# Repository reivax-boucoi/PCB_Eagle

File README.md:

# PCB
This repo contains Eagle files from personnal projects involving PCBs.

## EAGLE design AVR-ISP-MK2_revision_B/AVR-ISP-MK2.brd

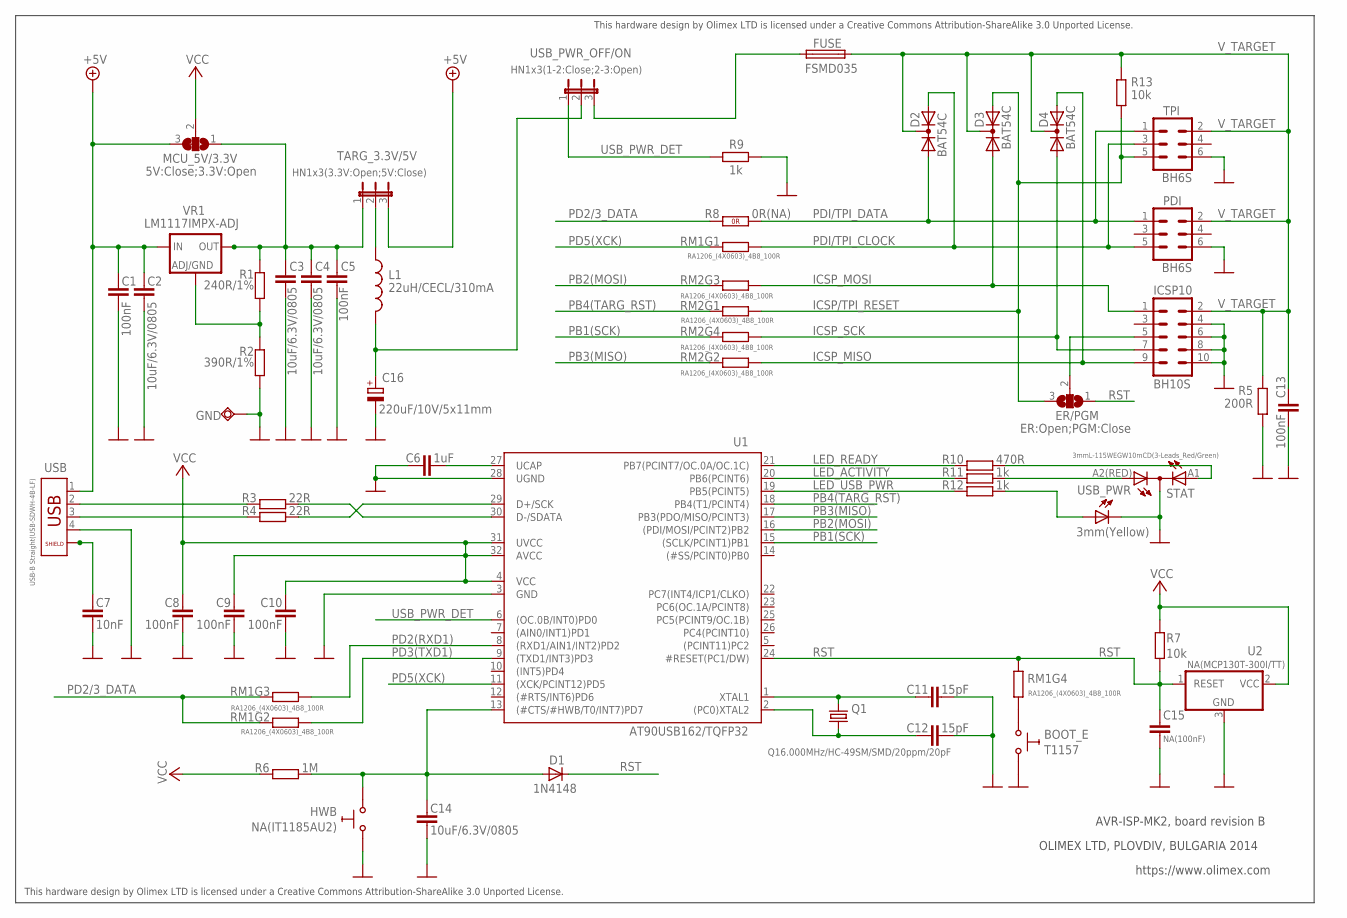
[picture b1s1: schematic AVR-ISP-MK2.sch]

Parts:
BOOT_E: T1157
C1, C5, C8, C9, C10, C13: 100nF; C0603_DWS
C2, C3, C4, C14: 10uF/6.3V/0805; C0805_5MIL_DWS
C6: 1uF; C0603_DWS
C7: 10nF; C0603_DWS
C11, C12: 15pF; C0603_DWS
C15: NA(100nF); C0603_DWS_NA
C16: 220uF/10V/5x11mm; C-SMD5X11
D1: 1N4148; MINI-MELF
D2, D3, D4: BAT54C; SOT23C
ER/PGM: ER:Open;PGM:Close; SJ_2
FUSE: FSMD035; 1206
GND: TESTPAD3; TEST_PAD40/70/SQUARE
HWB: NA(IT1185AU2); IT1185AU2
ICSP10: BH10S; ML10_PADS
L1: 22uH/CECL/310mA; L_CECL
MCU_5V/3.3V: 5V:Close;3.3V:Open; SJ_2
PDI: BH6S; ML6_PADS
Q1: Q16.000MHz/HC-49SM/SMD/20ppm/20pF; HC49/SMD2_THIN
R1: 240R/1%; R0603_5MIL_DWS
R2: 390R/1%; R0603_5MIL_DWS
R3, R4: 22R; R0603_5MIL_DWS
R5: 200R; R0805_5MIL_DWS
R6: 1M; R0603_5MIL_DWS
R7, R13: 10k; R0603_5MIL_DWS
R8: 0R(NA); 0603_0R
R9, R11, R12: 1k; R0603_5MIL_DWS
R10: 470R; R0603_5MIL_DWS
RM1, RM2: RA1206_(4X0603)_4B8_100R; R_MATRIX_4
STAT: 3mmL-115WEGW10mCD(3-Leads_Red/Green); 2X3MMLED
TARG_3.3V/5V: HN1x3(3.3V:Open;5V:Close); HN1X3-SMD_MIRROR
TPI: BH6S; ML6_PADS
U1: AT90USB162/TQFP32; TQFP32
U2: NA(MCP130T-300I/TT); SOT23
USB: USB-B Straight(USB-SDWH-4B-LF); USB_PADS
USB_PWR: 3mm(Yellow); LED-3.0MM
USB_PWR_OFF/ON: HN1x3(1-2:Close;2-3:Open); HN1X3-SMD
VR1: LM1117IMPX-ADJ; SOT223_

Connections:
+5V: C1.1, C2.1, MCU_5V/3.3V.3, TARG_3.3V/5V.3, USB.1, VR1.3 (IN)
GND: BOOT_E.2 (1), C1.2, C2.2, C3.2, C4.2, C5.2, C6.2, C7.2, C8.2, C9.2, C10.2, C11.1, C12.1, C13.2, C14.2, C15.2, C16.-, GND.P$1, HWB.2 (1), ICSP10.4, ICSP10.6, ICSP10.8, ICSP10.10, PDI.6, R2.2, R5.2, R9.1, STAT.C, TPI.6, U1.3 (GND), U1.28 (UGND), U2.3 (GND), USB.4, USB_PWR.K (C)
ICSP/TPI_RESET: D3.1 (A1), ER/PGM.3, R13.2, RM2.1.2 (2), TPI.5
ICSP_MISO: D4.1 (A1), ICSP10.9, RM2.2.2 (2)
ICSP_MOSI: D3.2 (A2), ICSP10.1, RM2.3.2 (2)
ICSP_SCK: D4.2 (A2), ICSP10.7, RM2.4.2 (2)
LED_ACTIVITY: R11.2, U1.20 (PB6(PCINT6))
LED_READY: R10.2, U1.21 (PB7(PCINT7/OC.0A/OC.1C))
LED_USB_PWR: R12.2, U1.19 (PB5(PCINT5))
unnamed: C14.1, D1.A, HWB.1 (0), R6.2, U1.13 ((#CTS/#HWB/T0/INT7)PD7)
unnamed: C7.1, USB.P$5 (5), USB.P$6 (6)
unnamed: R11.1, STAT.A2(RED) (AR)
unnamed: R12.1, USB_PWR.A
unnamed: C3.1, C4.1, C5.1, MCU_5V/3.3V.1, R1.1, TARG_3.3V/5V.1, VR1.2 (OUT), VR1.4 (RAD)
unnamed: R1.2, R2.1, VR1.1 (ADJ/GND)
unnamed: BOOT_E.1 (0), RM1.4.1 (1)
unnamed: L1.1, TARG_3.3V/5V.2
unnamed: C16.+, L1.2, USB_PWR_OFF/ON.2
unnamed: C6.1, U1.27 (UCAP)
unnamed: ER/PGM.2, ICSP10.5
unnamed: FUSE.1, USB_PWR_OFF/ON.3
unnamed: R10.1, STAT.A1 (AG)
unnamed: C11.2, Q1.2, U1.1 (XTAL1)
unnamed: C12.2, Q1.1, U1.2 ((PC0)XTAL2)
unnamed: R3.2, U1.30 (D-/SDATA)
unnamed: R4.2, U1.29 (D+/SCK)
unnamed: R3.1, USB.2
unnamed: R4.1, USB.3
PB1(SCK): RM2.4.1 (1), U1.15 ((SCLK/PCINT1)PB1)
PB2(MOSI): RM2.3.1 (1), U1.16 ((PDI/MOSI/PCINT2)PB2)
PB3(MISO): RM2.2.1 (1), U1.17 (PB3(PDO/MISO/PCINT3))
PB4(TARG_RST): RM2.1.1 (1), U1.18 (PB4(T1/PCINT4))
PD2(RXD1): RM1.3.1 (1), U1.8 ((RXD1/AIN1/INT2)PD2)
PD2/3_DATA: R8.1 (1.1), RM1.2.2 (2), RM1.3.2 (2)
PD3(TXD1): RM1.2.1 (1), U1.9 ((TXD1/INT3)PD3)
PD5(XCK): RM1.1.1 (1), U1.11 ((XCK/PCINT12)PD5)
PDI/TPI_CLOCK: D2.2 (A2), PDI.5, RM1.1.2 (2), TPI.3
PDI/TPI_DATA: D2.1 (A1), PDI.1, R8.2 (1.2), TPI.1
RST: C15.1, D1.C (K), ER/PGM.1, R7.2, RM1.4.2 (2), U1.24 (#RESET(PC1/DW)), U2.1 (RESET)
USB_PWR_DET: R9.2, U1.6 ((OC.0B/INT0)PD0), USB_PWR_OFF/ON.1
VCC: C8.1, C9.1, C10.1, MCU_5V/3.3V.2, R6.1, R7.1, U1.4 (VCC), U1.31 (UVCC), U1.32 (AVCC), U2.2 (VCC)
V_TARGET: C13.1, D2.3 (K), D3.3 (K), D4.3 (K), FUSE.2, ICSP10.2, PDI.2, R5.1, R13.1, TPI.2

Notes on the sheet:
AVR-ISP-MK2, board revision B
OLIMEX LTD, PLOVDIV, BULGARIA 2014
https://www.olimex.com
This hardware design by Olimex LTD is licensed under a Creative Commons Attribution-ShareAlike 3.0 Unported License.

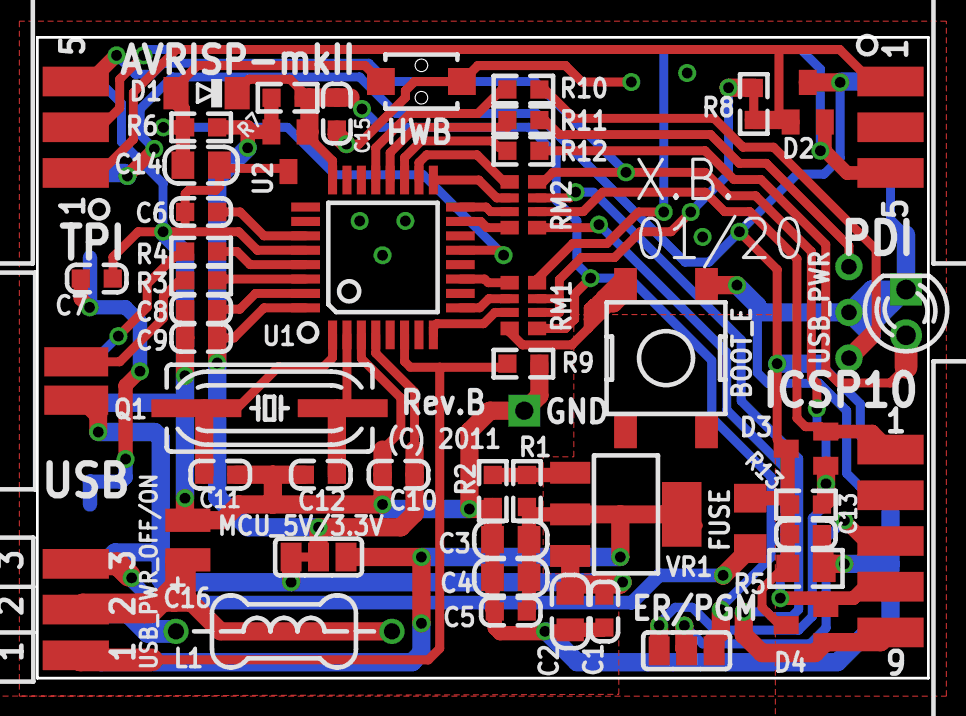
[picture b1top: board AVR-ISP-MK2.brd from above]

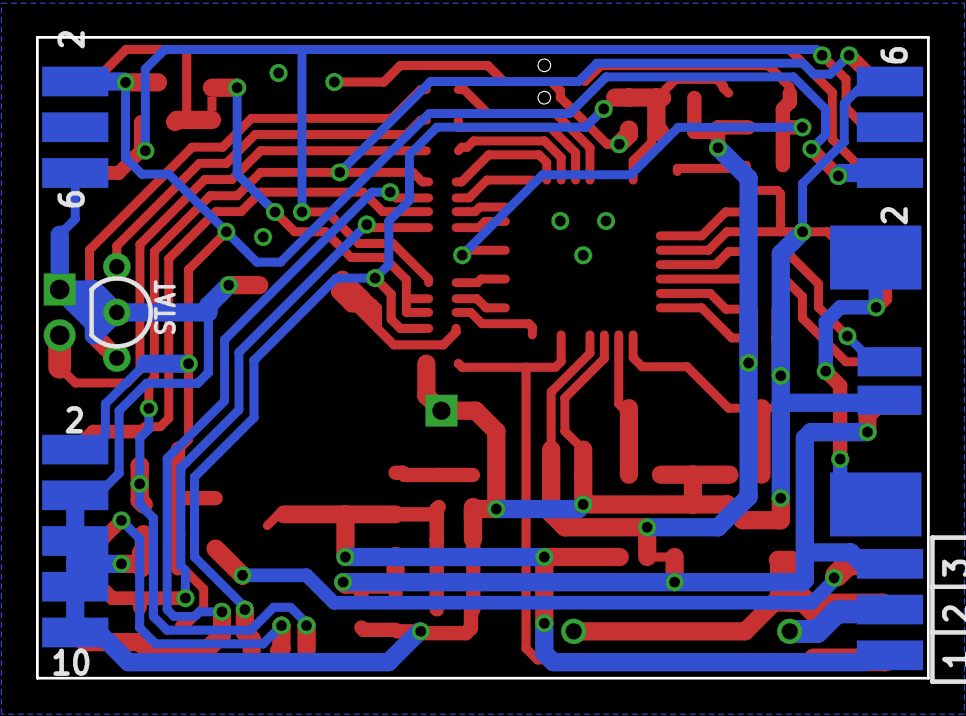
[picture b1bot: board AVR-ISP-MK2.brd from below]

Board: 2 copper layers, 49.5 x 35.6 mm, 54 parts (2 on the bottom side), 42 nets.

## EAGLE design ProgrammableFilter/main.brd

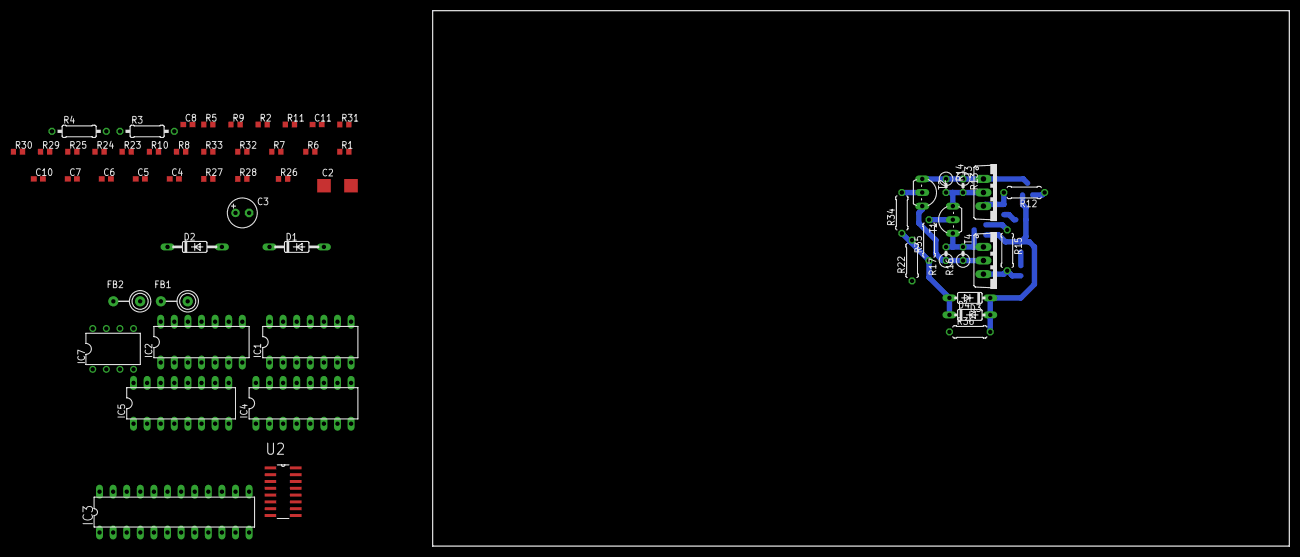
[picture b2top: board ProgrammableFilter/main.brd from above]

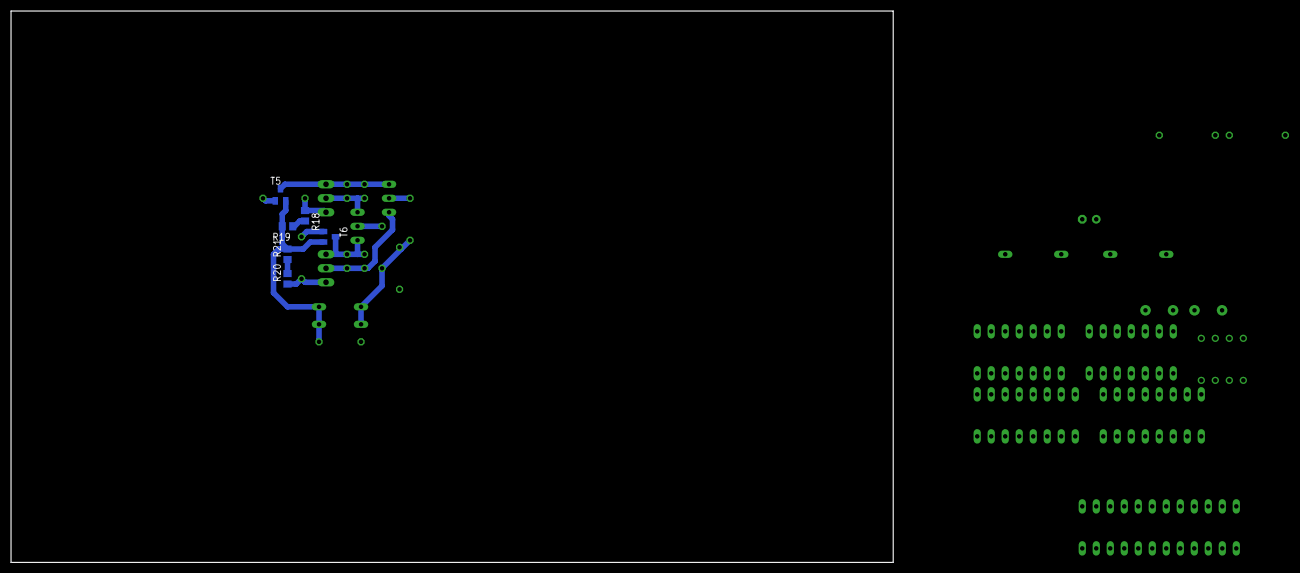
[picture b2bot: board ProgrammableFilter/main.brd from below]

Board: 2 copper layers, 160.0 x 100.0 mm, 64 parts (6 on the bottom side), 58 nets.

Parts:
C2: C/6032-28R
C3: E2,5-6
C4: 100n; C0603
C5, C7: 100p; C0603
C6: 220p; C0603
C8: 1n; C0603
C10: 120n; C0603
C11: 1u; C0603
D1, D2: 1N4148DO35-10; DO35-10
D3, D4: 1N4148DO35-7; DO35-7
FB1, FB2: FB
IC1: TL074P; DIL14
IC2: LM324N; DIL14
IC3: MAX261; DIL24-3
IC4, IC5: 4053N; DIL16
IC7: TL072P; DIL08
R1, R32: 180k; R0603
R2: 20k; R0603
R3: 47k 1/2W; 0207/10
R4: 1M; 0207/10
R5: 1M; R0603
R6, R7: 100k; R0603
R8, R10: 4.7k; R0603
R9, R11: 18k; R0603
R12, R15, R36: 1k; 0207/7
R13, R14, R16, R17: 2k; 0207/2V
R18, R19, R20, R21: 1; R0805
R22: 100; 0207/7
R23, R24, R25: 10k; R0603
R26: 38k668; R0603
R27: 4k337; R0603
R28: 12k333; R0603
R29: 1k; R0603
R30: 47k; R0603
R31: 84k; R0603
R33: 168k; R0603
R34, R35: FB; 0207/7
T1: 2N2222; TO92-EBC-OVAL
T2: TO92-EBC
T3, T4: TO220V
T5, T6: SOT23-BEC
U2: ADG509AKR; SOIC127P600X175-16N

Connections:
+5V: D1.C, IC3.9
+15V: R13.2, R14.2, T1.C, T3.2
-5V: D2.A, IC3.16, R33.1
-15V: R16.1, R17.1, T2.C, T4.2
AGND: C5.2, C7.2, C11.2, IC2.12, IC3.17, IC4.1, IC4.3, IC5.4, R4.1, R5.1
GND: IC4.8, IC5.8
unnamed: D1.A, D2.C, IC1.3, R3.2
unnamed: IC3.24, U2.12
unnamed: R3.1, R4.2
unnamed: IC1.5, IC4.15
unnamed: IC1.6, R6.2, R7.1
unnamed: C4.2, IC4.2, IC4.14, R5.2, R7.2
unnamed: C6.1, IC1.8, IC1.9, R10.2
unnamed: IC1.7, R6.1, R8.2
unnamed: C6.2, R8.1, R9.2
unnamed: C5.1, IC1.10, R9.1
unnamed: C8.1, IC1.13, IC1.14, R1.2
unnamed: IC5.14, IC7.5
unnamed: C8.2, R10.1, R11.2
unnamed: C7.1, IC1.12, R11.1
unnamed: IC3.3, U2.11
unnamed: IC3.1, U2.10
unnamed: C4.1, IC1.1, IC1.2, IC4.12
unnamed: IC3.22, U2.5
unnamed: IC3.21, U2.6
unnamed: IC3.20, U2.7
unnamed: IC3.5, R1.1, R2.1, U2.4
unnamed: IC4.4, R2.2
unnamed: IC7.6, IC7.7, R23.1
unnamed: D3.C, D4.A, R19.2, R21.2, R36.2, T5.E, T6.E
unnamed: R16.2, R17.2, T1.E, T4.1, T6.C
unnamed: R15.1, T6.B
unnamed: R15.2, R20.1, T4.3
unnamed: R12.1, T5.B
unnamed: R12.2, R18.1, T3.3
unnamed: R13.1, R14.1, T2.E, T3.1, T5.C
unnamed: IC3.23, IC5.12, U2.8, U2.13
unnamed: R18.2, R19.1
unnamed: R20.2, R21.1
unnamed: IC5.13, U2.9
unnamed: R35.2, T1.B
unnamed: IC7.3, R23.2, R24.2
unnamed: IC5.2, R26.1
unnamed: IC5.1, R27.1
unnamed: IC5.5, R28.1
unnamed: IC5.3, R29.1
unnamed: IC5.15, IC7.2, R25.1
unnamed: R26.2, R27.2, R28.2, R29.2
unnamed: IC7.1, R25.2
unnamed: C10.1, IC2.14, R24.1, R32.2
unnamed: C10.2, IC2.13, R30.1
unnamed: C11.1, R30.2, R31.1, R32.1, R33.2
unnamed: D3.A, D4.C, R22.2, R34.1, R35.1
unnamed: R34.2, T2.B
V+: IC1.4, IC2.4, IC7.8
V-: IC1.11, IC2.11, IC7.4
VCC: IC4.16, IC5.16
VEE: IC4.7, IC5.7

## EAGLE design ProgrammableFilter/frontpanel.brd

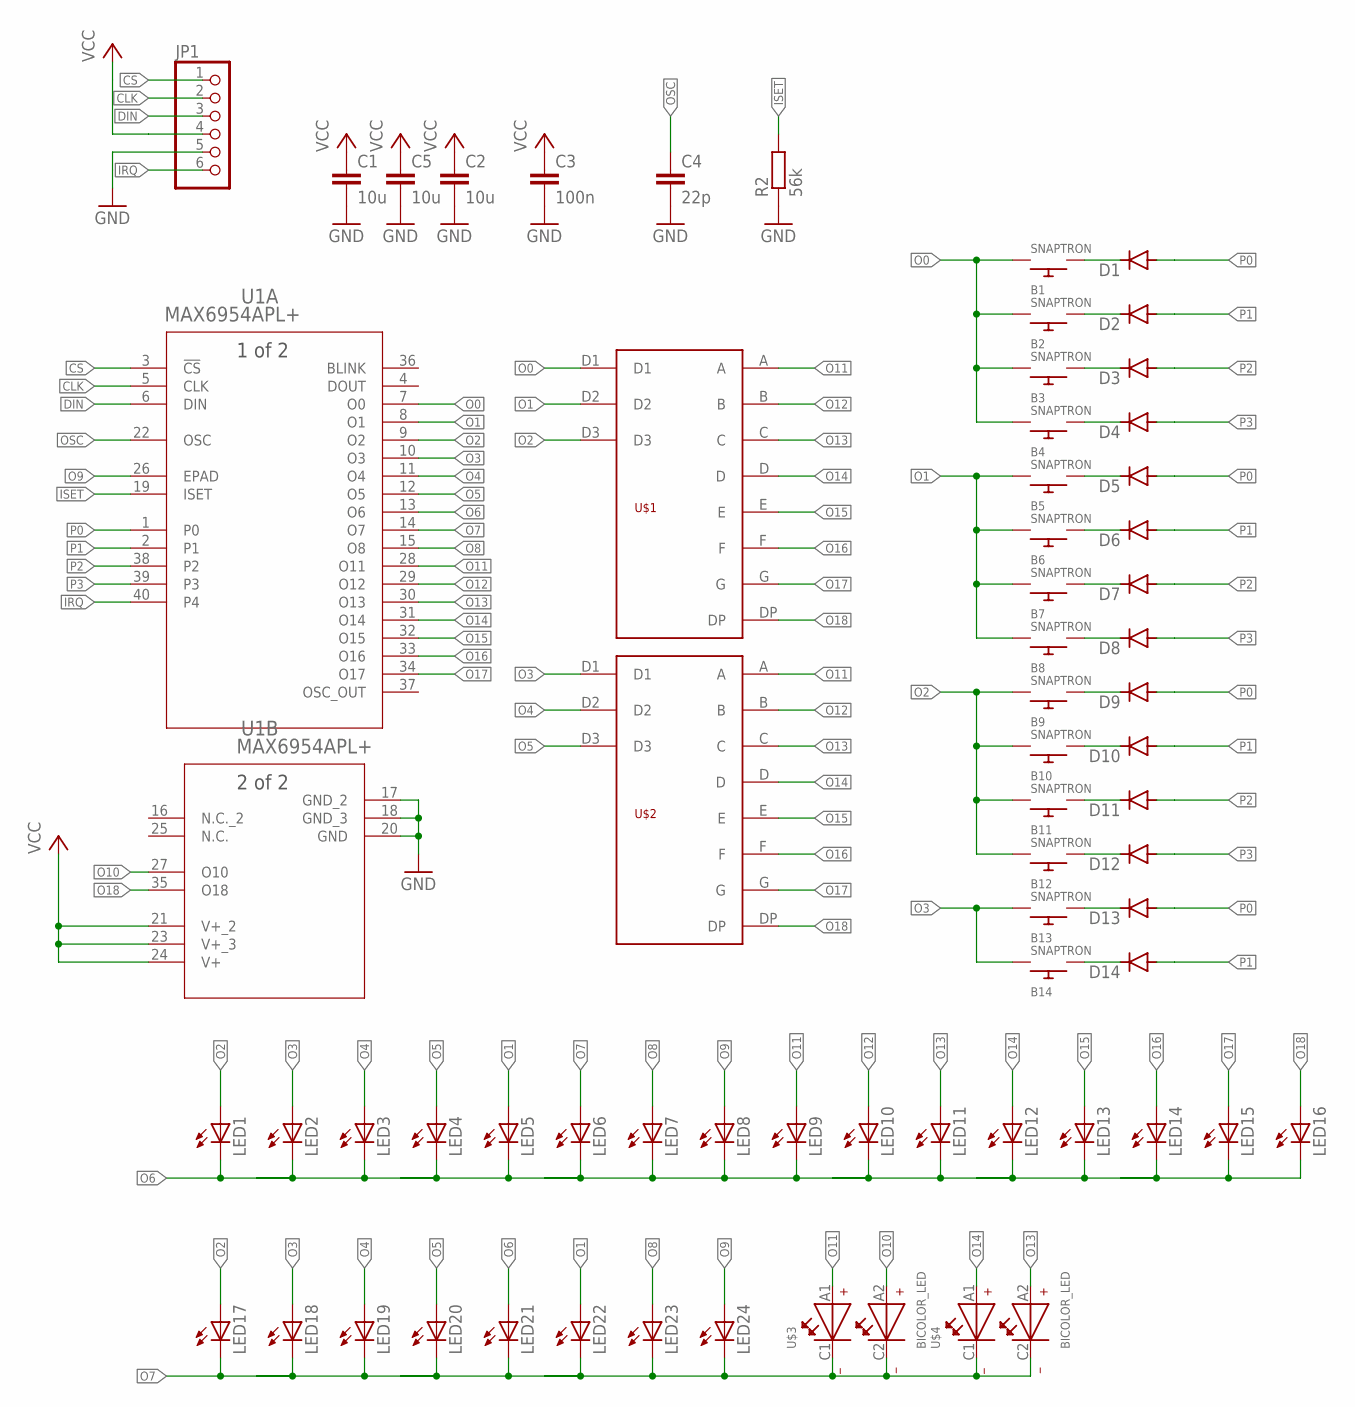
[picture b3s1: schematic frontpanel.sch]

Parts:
B1, B2, B3, B4, B5, B6, B7, B8, B9, B10, B11, B12, B13, B14: SNAPTRON; SNAPTRON-8.5
C1, C2, C5: 10u; C0805
C3: 100n; C0805
C4: 22p; C0805
D1, D2, D3, D4, D5, D6, D7, D8, D9, D10, D11, D12, D13, D14: 1N4148DO35-10; DO35-10
JP1: PINHD-1X6; 1X06
LED1, LED2, LED3, LED4, LED5, LED6, LED7, LED8, LED9, LED10, LED11, LED12, LED13, LED14, LED15, LED16, LED17, LED18, LED19, LED20, LED21, LED22, LED23, LED24: LEDCHIP-LED0805; CHIP-LED0805
R2: 56k; R0805
U1: MAX6954APL+; 21-0044B_40_MXM
U$1, U$2: 3-DIGIT_7-SEGMENT-DISPLAY
U$3, U$4: BICOLOR_LED

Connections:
!CS: JP1.1, U1.3 (!CS)
!IRQ: JP1.6, U1.40 (P4)
CLK: JP1.2, U1.5 (CLK)
DIN: JP1.3, U1.6 (DIN)
GND: C1.2, C2.2, C3.2, C4.2, C5.2, JP1.5, R2.1, U1.17 (GND_2), U1.18 (GND_3), U1.20 (GND)
ISET: R2.2, U1.19 (ISET)
unnamed: B1.P$2, D1.C
unnamed: B2.P$2, D2.C
unnamed: B5.P$2, D5.C
unnamed: B3.P$2, D3.C
unnamed: B4.P$2, D4.C
unnamed: B6.P$2, D6.C
unnamed: B7.P$2, D7.C
unnamed: B8.P$2, D8.C
unnamed: B9.P$2, D9.C
unnamed: B10.P$2, D10.C
unnamed: B11.P$2, D11.C
unnamed: B12.P$2, D12.C
unnamed: B13.P$2, D13.C
unnamed: B14.P$2, D14.C
O0: B1.P$1, B2.P$1, B3.P$1, B4.P$1, U1.7 (O0), U$1.D1
O1: B5.P$1, B6.P$1, B7.P$1, B8.P$1, LED5.A, LED22.A, U1.8 (O1), U$1.D2
O2: B9.P$1, B10.P$1, B11.P$1, B12.P$1, LED1.A, LED17.A, U1.9 (O2), U$1.D3
O3: B13.P$1, B14.P$1, LED2.A, LED18.A, U1.10 (O3), U$2.D1
O4: LED3.A, LED19.A, U1.11 (O4), U$2.D2
O5: LED4.A, LED20.A, U1.12 (O5), U$2.D3
O6: LED1.C, LED2.C, LED3.C, LED4.C, LED5.C, LED6.C, LED7.C, LED8.C, LED9.C, LED10.C, LED11.C, LED12.C, LED13.C, LED14.C, LED15.C, LED16.C, LED21.A, U1.13 (O6)
O7: LED6.A, LED17.C, LED18.C, LED19.C, LED20.C, LED21.C, LED22.C, LED23.C, LED24.C, U1.14 (O7), U$3.C1, U$3.C2, U$4.C1, U$4.C2
O8: LED7.A, LED23.A, U1.15 (O8)
O9: LED8.A, LED24.A, U1.26 (EPAD)
O10: U1.27 (O10), U$3.A2
O11: LED9.A, U1.28 (O11), U$1.A, U$2.A, U$3.A1
O12: LED10.A, U1.29 (O12), U$1.B, U$2.B
O13: LED11.A, U1.30 (O13), U$1.C, U$2.C, U$4.A2
O14: LED12.A, U1.31 (O14), U$1.D, U$2.D, U$4.A1
O15: LED13.A, U1.32 (O15), U$1.E, U$2.E
O16: LED14.A, U1.33 (O16), U$1.F, U$2.F
O17: LED15.A, U1.34 (O17), U$1.G, U$2.G
O18: LED16.A, U1.35 (O18), U$1.DP, U$2.DP
OSC: C4.1, U1.22 (OSC)
P0: D1.A, D5.A, D9.A, D13.A, U1.1 (P0)
P1: D2.A, D6.A, D10.A, D14.A, U1.2 (P1)
P2: D3.A, D7.A, D11.A, U1.38 (P2)
P3: D4.A, D8.A, D12.A, U1.39 (P3)
VCC: C1.1, C2.1, C3.1, C5.1, JP1.4, U1.21 (V+_2), U1.23 (V+_3), U1.24 (V+)

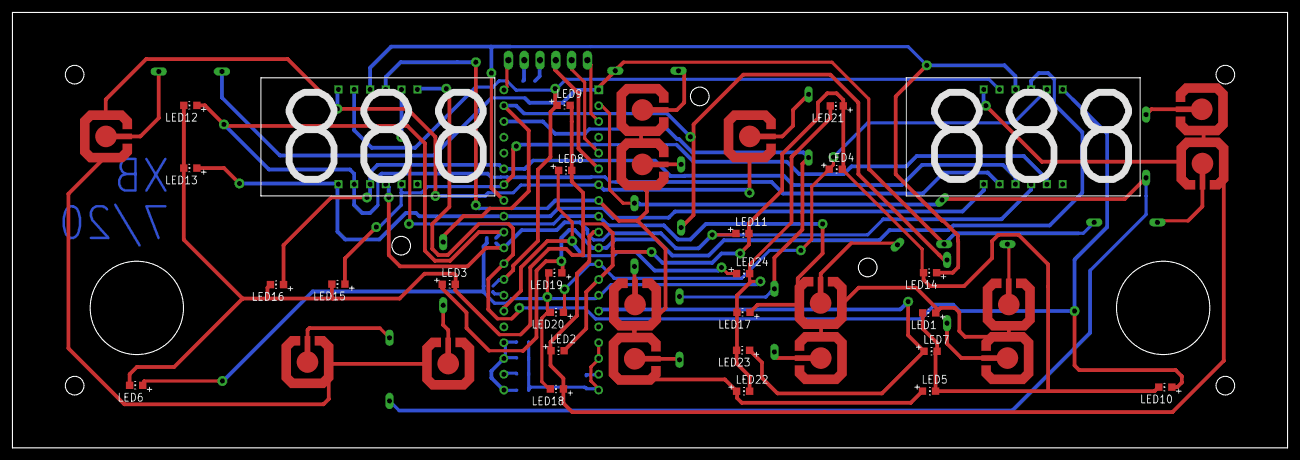
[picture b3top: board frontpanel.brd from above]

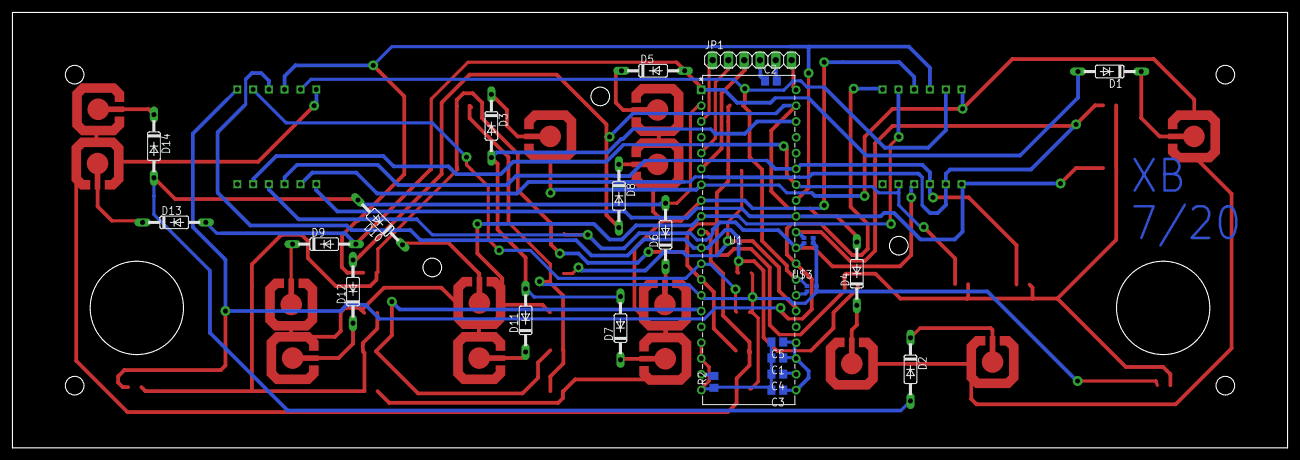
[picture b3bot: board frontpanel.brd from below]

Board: 2 copper layers, 205.0 x 70.0 mm, 64 parts (24 on the bottom side), 45 nets.

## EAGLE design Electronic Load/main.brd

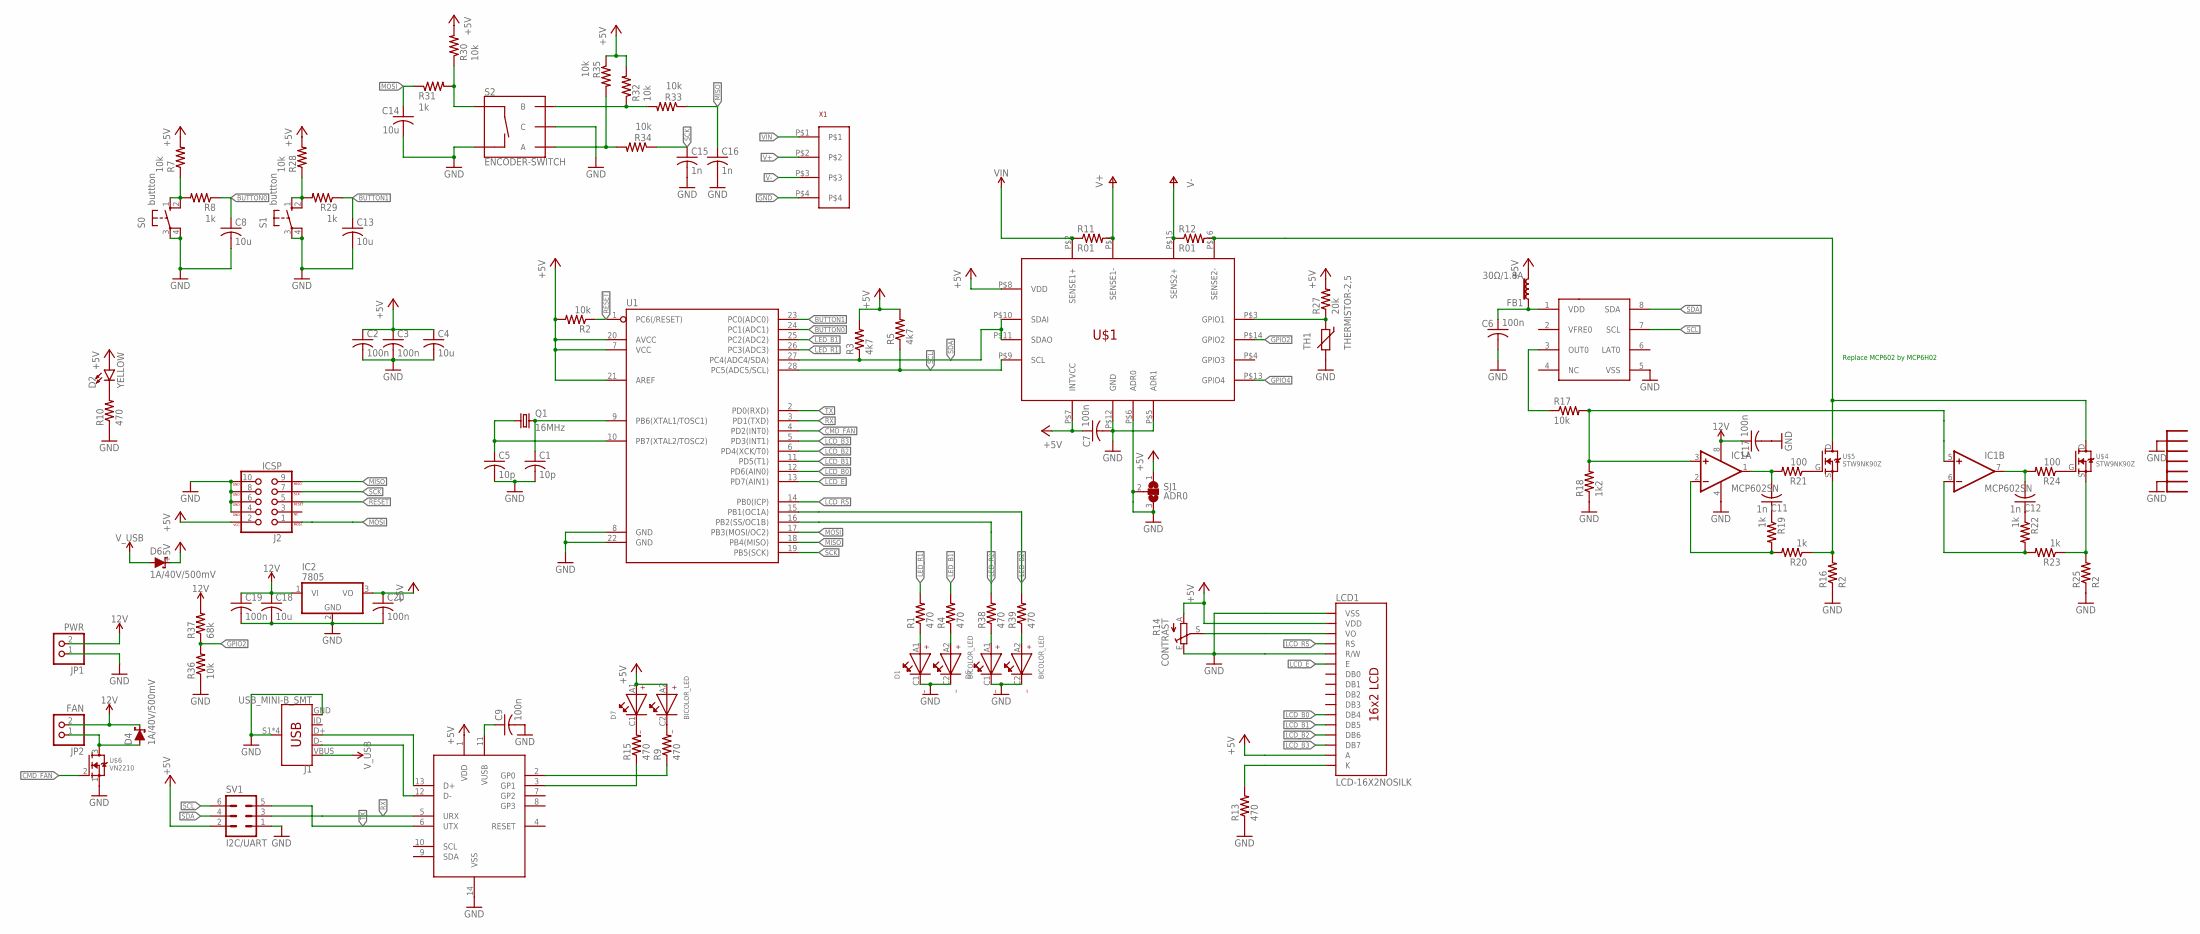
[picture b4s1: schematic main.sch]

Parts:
BR1: MCP2221A; DIP14
C1, C5: 10p; C0603
C2, C3, C6, C7, C9, C17, C19, C20: 100n; C0603
C4, C18: 10u; C1206
C8, C13, C14: 10u; C0603
C11, C12: 1n; C0805
C15, C16: 1n; C0603
D1, D5, D7: BICOLOR_LED
D2: YELLOW; LED_3MM
D4, D6: 1A/40V/500mV; SMA-DIODE
FB1: 30Ω/1.8A; 0603
IC1: MCP602SN; SO08
IC2: 7805; TO220V
J1: USB_MINI-B_SMT; USB-MINIB
J2: ICSP; 2X5-SHROUDED
JP1: PWR; 1X02
JP2: FAN; 1X02
LCD1: LCD-16X2NOSILK; LCD-16X2_NOSILK
Q1: 16MHz; HC49U70
R1, R4, R9, R10, R13, R15, R38, R39: 470; R0805
R2, R7, R17, R28, R30, R32, R33, R34, R35, R36: 10k; R0805
R3, R5: 4k7; R0805
R8, R19, R20, R22, R23, R29, R31: 1k; R0805
R11, R12: R01; R2512
R14: CONTRAST; RJ9W
R16, R25: R2; R2512
R18: 1k2; R0805
R21, R24: 100; R0805
R27: 20k; R0805
R37: 68k; R0805
S0, S1: buttton; B3F-10XX
S2: ENCODER-SWITCH; ROTARY_ENC_PLAIN
SJ1: ADR0; SJ_2
SV1: I2C/UART; MA03-2
TH1: THERMISTOR-2,5; RS-2,5
U1: 328P; DIP28
U$1: LTC2992; MSOP16
U$2: HEATSINK_0NOSILK; HEATSINK_01
U$3: MCP47FEB21; TSSOP8
U$4, U$5: STW9NK90Z; TO247BV
U$6: VN2210; TO92
X1: SCREWTERM_5MM_4WAY

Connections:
12V: C17.1, C18.1, C19.1, D4.C, IC1.8 (V+), IC2.1 (VI), JP1.2, JP2.2, R37.2
+5V: BR1.1 (VDD), C2.1, C3.1, C4.1, C7.1, C20.1, D2.A, D6.C, D7.A1, D7.A2, FB1.2, IC2.3 (VO), J2.2 (VCC), LCD1.2 (VDD), LCD1.15 (A), R2.2, R3.2, R5.2, R7.2, R14.A, R27.2, R28.2, R30.2, R32.2, R35.1, SJ1.1, SV1.2, U1.7 (VCC), U1.20 (AVCC), U1.21 (AREF), U$1.P$7 (INTVCC), U$1.P$8 (VDD)
B0: R7.1, R8.2, S0.1 (S), S0.2 (S1)
B1: R28.1, R29.2, S1.1 (S), S1.2 (S1)
BUTTON0: C8.1, R8.1, U1.24 (PC1(ADC1))
BUTTON1: C13.1, R29.1, U1.23 (PC0(ADC0))
CMD_FAN: U1.4 (PD2(INT0)), U$6.2 (G)
D+: BR1.13 (D+), J1.D+
D-: BR1.12 (D-), J1.D-
DAC_OUT: R17.1, U$3.3 (OUT0)
FANNEG: D4.A, JP2.1, U$6.3 (D)
GND: BR1.14 (VSS), C1.2, C2.2, C3.2, C4.2, C5.2, C6.2, C7.2, C8.2, C9.2, C13.2, C14.2, C15.2, C16.2, C17.2, C18.2, C19.2, C20.2, D1.C1, D1.C2, D5.C1, D5.C2, IC1.4 (V-), IC2.2 (GND), J1.GND, J1.S1 (SHIELD), J1.S2 (SHIELD), J1.S3 (SHIELD), J1.S4 (SHIELD), J2.4 (GND), J2.6 (GND), J2.8 (GND), J2.10 (GND), JP1.1, LCD1.1 (VSS), LCD1.5 (R/W), R10.1, R13.1, R14.E, R16.1, R18.1, R25.1, R36.1, S0.3, S0.4 (P1), S1.3, S1.4 (P1), S2.C, S2.SW-, SJ1.2, SJ1.3, SV1.1, TH1.2, U1.8 (GND), U1.22 (GND), U$1.P$5 (ADR1), U$1.P$6 (ADR0), U$1.P$12 (GND), U$2.P$1, U$2.P$2, U$3.5 (VSS), U$6.1 (S), X1.P$4
GPIO2: R36.2, R37.1, U$1.P$14 (GPIO2)
GPIO4: U$1.P$13 (GPIO4)
LCD1_CONTRAST: LCD1.3 (VO), R14.S
LCD1_K: LCD1.16 (K), R13.2
LCD_B0: LCD1.11 (DB4), U1.12 (PD6(AIN0))
LCD_B1: LCD1.12 (DB5), U1.11 (PD5(T1))
LCD_B2: LCD1.13 (DB6), U1.6 (PD4(XCK/T0))
LCD_B3: LCD1.14 (DB7), U1.5 (PD3(INT1))
LCD_E: LCD1.6 (E), U1.13 (PD7(AIN1))
LCD_RS: LCD1.4 (RS), U1.14 (PB0(ICP))
LED_B1: R4.2, U1.25 (PC2(ADC2))
LED_B2: R39.2, U1.15 (PB1(OC1A))
LED_R1: R1.2, U1.26 (PC3(ADC3))
LED_R2: R38.2, U1.16 (PB2(SS/OC1B))
MISO: C16.1, J2.9 (MISO), R33.1, U1.18 (PB4(MISO))
MOSI: C14.1, J2.1 (MOSI), R31.1, U1.17 (PB3(MOSI/OC2))
unnamed: C1.1, Q1.2, U1.9 (PB6(XTAL1/TOSC1))
unnamed: C5.1, Q1.1, U1.10 (PB7(XTAL2/TOSC2))
unnamed: C6.1, FB1.1, U$3.1 (VDD)
unnamed: D5.A1, R38.1
unnamed: D5.A2, R39.1
unnamed: D1.A1, R1.1
unnamed: R21.1, U$5.G
unnamed: D1.A2, R4.1
unnamed: BR1.2 (GP0), R9.1
unnamed: BR1.11 (VUSB), C9.1
unnamed: BR1.3 (GP1), R15.1
unnamed: D7.C1, R15.2
unnamed: D7.C2, R9.2
unnamed: D2.K (C), R10.2
unnamed: C11.1, R19.1
unnamed: C12.1, R22.1
unnamed: R12.2, U$1.P$16 (SENSE2-), U$4.D, U$5.D
RESET: J2.5 (RESET), R2.1, U1.1 (PC6(/RESET))
RX: BR1.5 (URX), SV1.3, U1.3 (PD1(TXD))
SCK: C15.1, J2.7 (SCK), R34.1, U1.19 (PB5(SCK))
SCL: R5.1, SV1.6, U1.28 (PC5(ADC5/SCL)), U$1.P$9 (SCL), U$3.7 (SCL)
SDA: R3.1, SV1.4, U1.27 (PC4(ADC4/SDA)), U$1.P$10 (SDAI), U$1.P$11 (SDAO), U$3.8 (SDA)
TX: BR1.6 (UTX), SV1.5, U1.2 (PD0(RXD))
V+: R11.2, U$1.P$1 (SENSE1-), X1.P$2
V-: R12.1, U$1.P$15 (SENS2+), X1.P$3
VCTRL: IC1.3 (+IN), IC1.5 (+IN), R17.2, R18.2
VENC: R30.1, R31.2, S2.SW+
VENCA: R34.2, R35.2, S2.A
VENCB: R32.1, R33.2, S2.B
VFB1: IC1.2 (-IN), R19.2, R20.2
VFB2: IC1.6 (-IN), R22.2, R23.2
VG2: R24.1, U$4.G
VIN: R11.1, U$1.P$2 (SENSE1+), X1.P$1
VO1: C11.2, IC1.1 (OUT), R21.2
VO2: C12.2, IC1.7 (OUT), R24.2
VS1: R16.2, R20.1, U$5.S
VS2: R23.1, R25.2, U$4.S
VT: R27.1, TH1.1, U$1.P$3 (GPIO1)
V_USB: D6.A, J1.VBUS

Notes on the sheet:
Replace MCP602 by MCP6H02

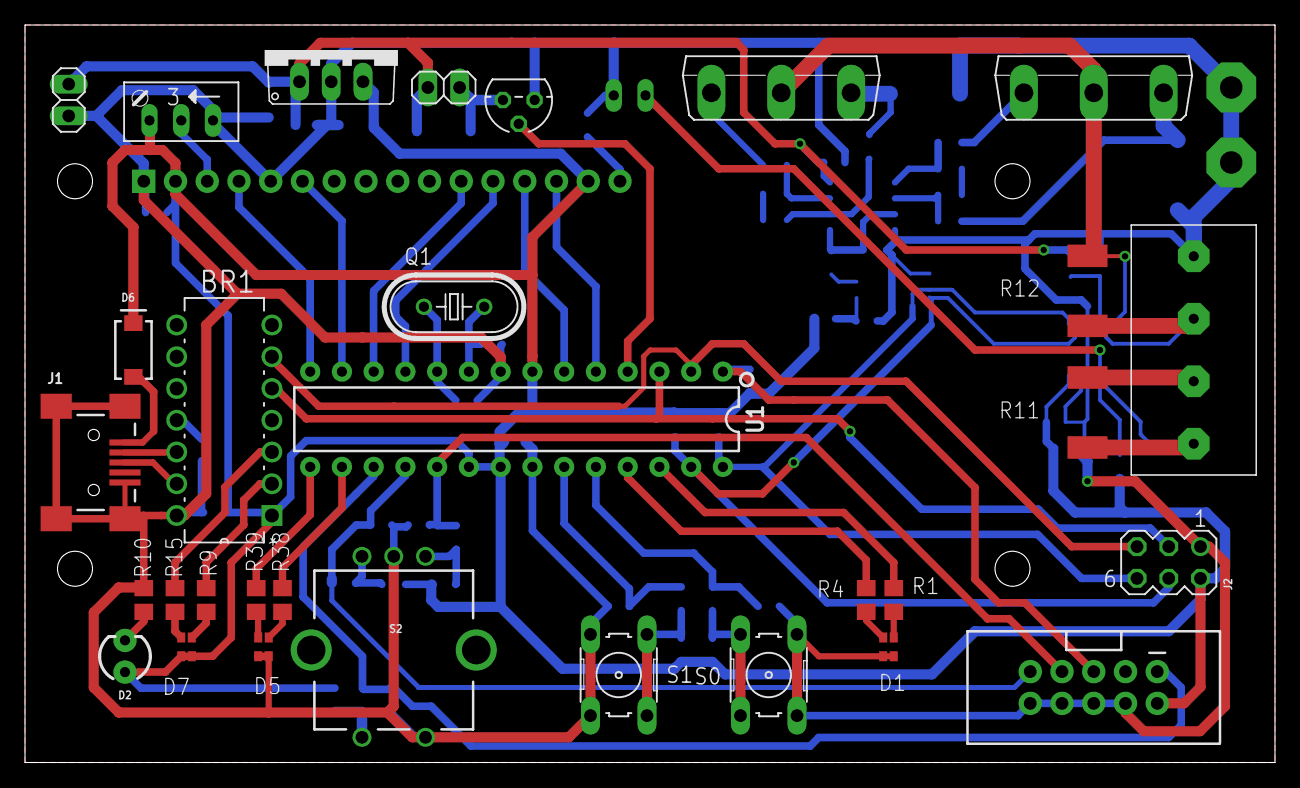
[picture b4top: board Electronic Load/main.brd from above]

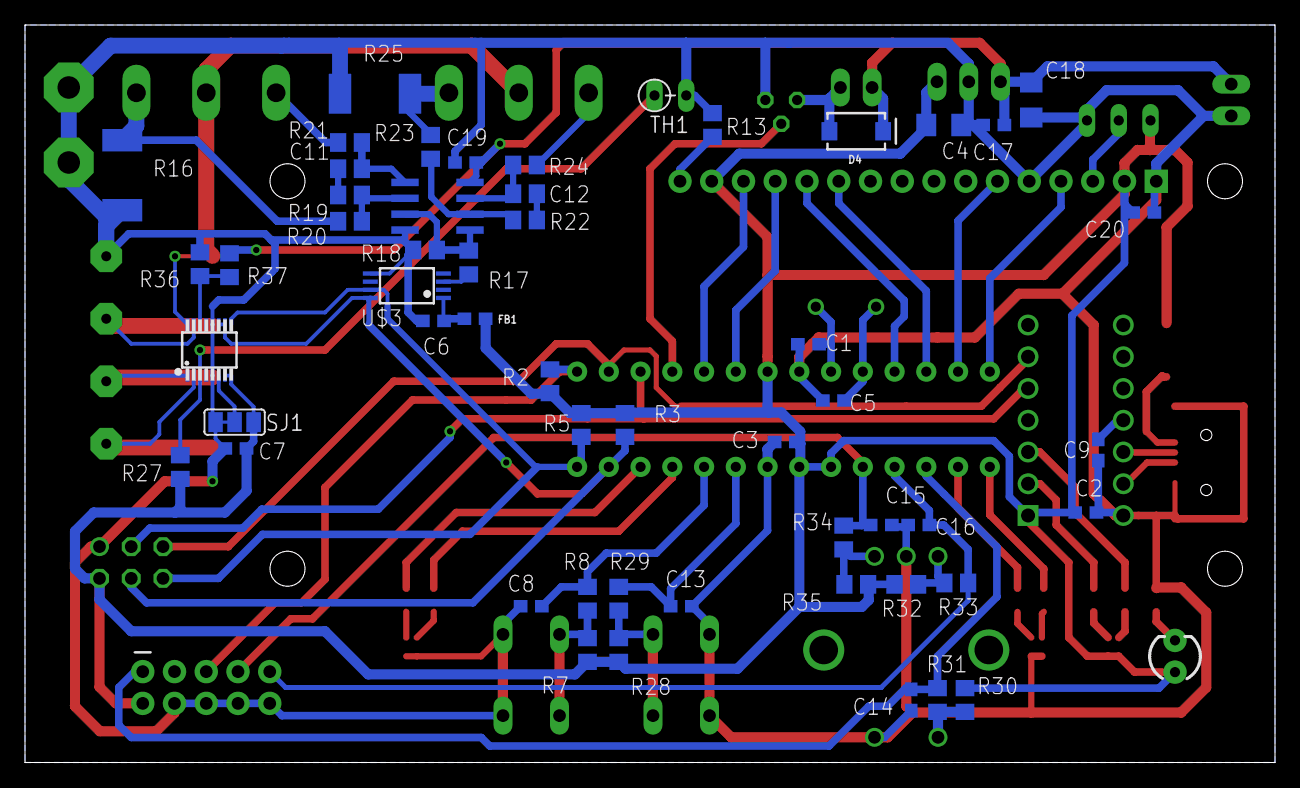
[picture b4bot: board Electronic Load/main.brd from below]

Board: 2 copper layers, 100.0 x 59.0 mm, 86 parts (53 on the bottom side), 66 nets.

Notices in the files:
AVR-ISP-MK2_revision_B/AVR-ISP-MK2.brd:
(C) 2011
parts and their libraries:
SparkFun-PowerSymbols: Licensing: Creative Commons ShareAlike 4.0 International - https://creativecommons.org/licenses/by-sa/4.0
Wurth_Elektronik_Electromechanic_Termina: Copyright: Würth Elektronik
